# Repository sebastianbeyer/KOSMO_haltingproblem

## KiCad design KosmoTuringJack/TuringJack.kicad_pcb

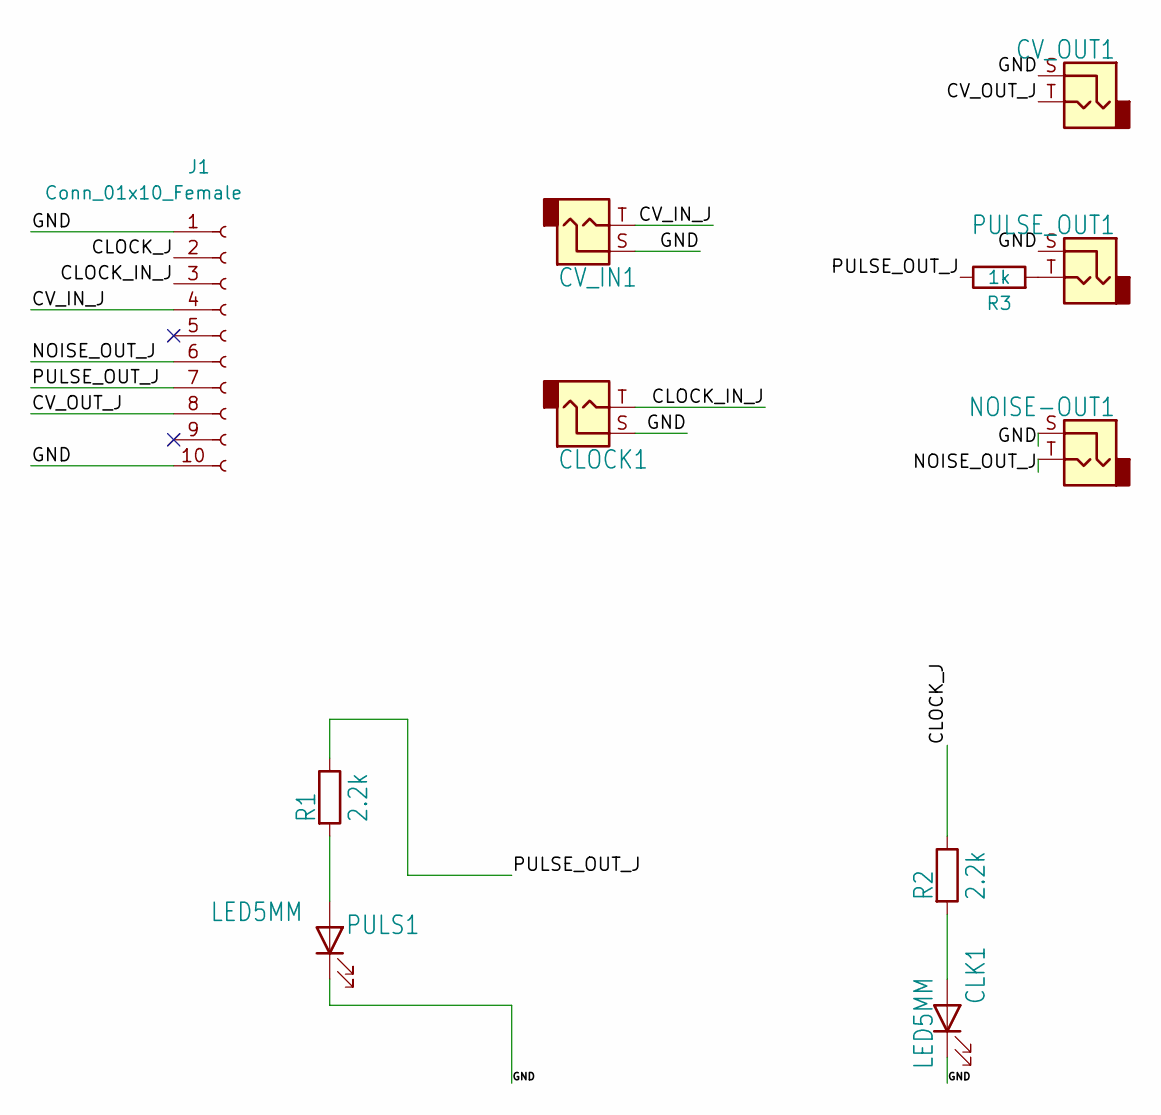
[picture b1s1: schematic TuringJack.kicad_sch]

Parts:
CLK1: LED5MM; LED_D5.0mm
CLOCK1: THONKICONNNEW; Jack_6.35mm_PJ_629HAN
CV_IN1: THONKICONNNEW; Jack_6.35mm_PJ_629HAN
CV_OUT1: THONKICONNNEW; Jack_6.35mm_PJ_629HAN
J1: Conn_01x10_Female; PinSocket_1x10_P2.54mm_Vertical
NOISE-OUT1: THONKICONNNEW; Jack_6.35mm_PJ_629HAN
PULS1: LED5MM; LED_D5.0mm
PULSE_OUT1: THONKICONNNEW; Jack_6.35mm_PJ_629HAN
R1, R2: 2.2k; R_Axial_DIN0207_L6.3mm_D2.5mm_P10.16mm_Horizontal
R3: 1k; R_Axial_DIN0207_L6.3mm_D2.5mm_P10.16mm_Horizontal

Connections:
/CLOCK_IN_J: CLOCK1.T, J1.3
/CLOCK_J: J1.2, R2.1
/CV_IN_J: CV_IN1.T, J1.4
/CV_OUT_J: CV_OUT1.T, J1.8
/GND: CLK1.1 (K), CLOCK1.S, CV_IN1.S, CV_OUT1.S, J1.1, J1.10, NOISE-OUT1.S, PULS1.1 (K), PULSE_OUT1.S
/NOISE_OUT_J: J1.6, NOISE-OUT1.T
/PULSE_OUT_J: J1.7, R1.1, R3.1
unnamed: CLK1.2 (A), R2.2
unnamed: PULS1.2 (A), R1.2
unnamed: PULSE_OUT1.T, R3.2

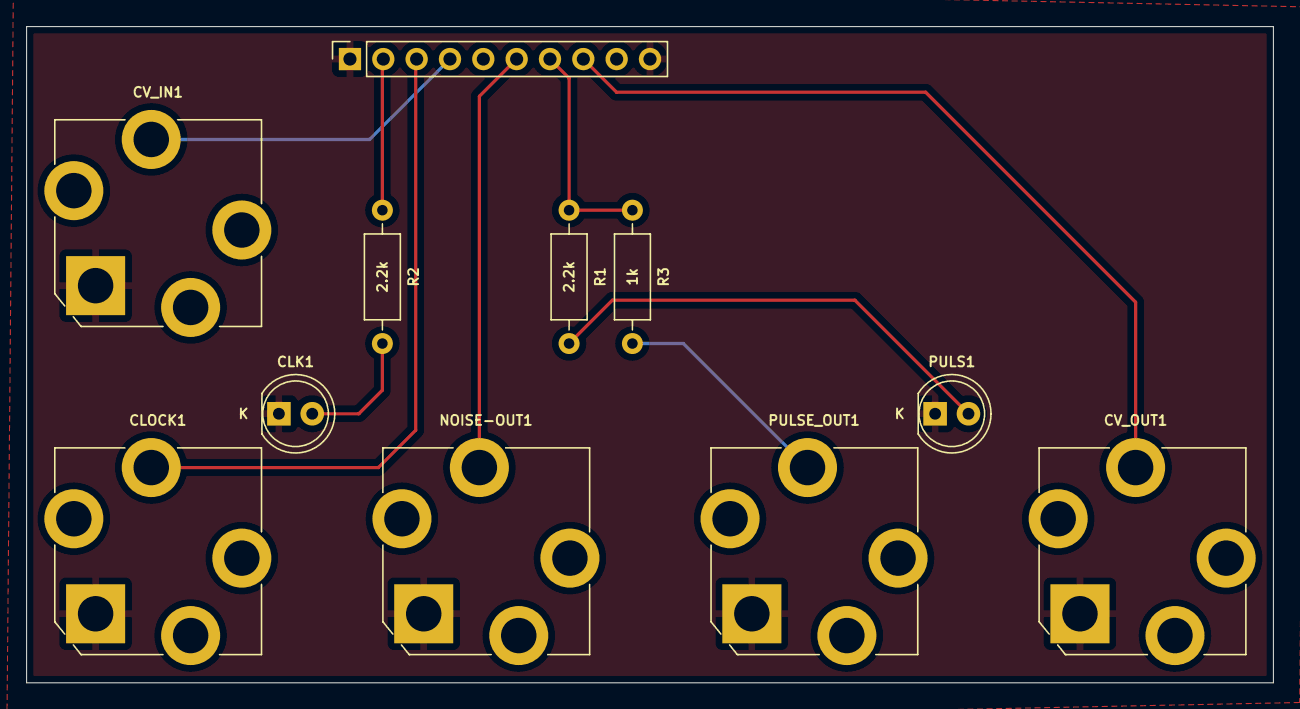
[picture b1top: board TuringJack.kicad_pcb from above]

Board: 2 copper layers, 95.0 x 50.0 mm, 11 parts (0 on the bottom side), 10 nets.

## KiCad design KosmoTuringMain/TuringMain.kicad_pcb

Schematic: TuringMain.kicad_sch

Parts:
AND_1, AND_2: 4081; DIL14
BUFFER1, BUFFER2: 4050; DIL16
C1, C5, C6, C7, C8, C13: 1n; C050-024X044
C2: 10n; C050-024X044
C3, C4, C15, C16, C17, C18, C19, C20, C21, C23, C24, C25, C26: 100n; C_Disc_D3.0mm_W1.6mm_P2.50mm
C9, C10, C12: 0.47uf; C050-035X075
C11: 330pf; C050-024X044
C14: 100n; C050-024X044
C22, C27: 10uf; CP_Radial_D6.3mm_P2.50mm
CHANGE1: 50k; Potentiometer_Alpha_RD901F-40-00D_Single_Vertical_centered
CLOCK1: THONKICONNNEW; Jack_6.35mm_PJ_629HAN
CV_IN1: THONKICONNNEW; Jack_6.35mm_PJ_629HAN
CV_OUT1: THONKICONNNEW; Jack_6.35mm_PJ_629HAN
D1: 1N4148; DO35-7
GATES1: MA08-2; IDC-Header_2x08_P2.54mm_Vertical
IC1: TL072P; DIL08
IC2, IC3: 78L09; TO-92_Inline_Wide
J1: Conn_01x10_Female; PinSocket_1x10_P2.54mm_Vertical
J2: Conn_01x10_Male; PinHeader_1x10_P2.54mm_Vertical
L1, L2: BL01RN1A
LENGTH1: ALPS-SRBV
NOISE-OUT1: THONKICONNNEW; Jack_6.35mm_PJ_629HAN
PULSES1: MA08-2; IDC-Header_2x08_P2.54mm_Vertical
PULSE_OUT1: THONKICONNNEW; Jack_6.35mm_PJ_629HAN
R1, R6, R7, R8, R12, R13, R14, R17, R23, R27: 10k; R_Axial_DIN0207_L6.3mm_D2.5mm_P10.16mm_Horizontal
R2: 3.3k; R_Axial_DIN0207_L6.3mm_D2.5mm_P10.16mm_Horizontal
R3, R5, R21, R24, R25: 100k; R_Axial_DIN0207_L6.3mm_D2.5mm_P10.16mm_Horizontal
R4, R9: 1.6k; R_Axial_DIN0207_L6.3mm_D2.5mm_P10.16mm_Horizontal
R10: 51k; R_Axial_DIN0207_L6.3mm_D2.5mm_P10.16mm_Horizontal
R11: 47k; R_Axial_DIN0207_L6.3mm_D2.5mm_P10.16mm_Horizontal
R15, R22, R26, R30: 1k; R_Axial_DIN0207_L6.3mm_D2.5mm_P10.16mm_Horizontal
R16: 5.1k; R_Axial_DIN0207_L6.3mm_D2.5mm_P10.16mm_Horizontal
R18: 68k; R_Axial_DIN0207_L6.3mm_D2.5mm_P10.16mm_Horizontal
R19, R29: 470k; R_Axial_DIN0207_L6.3mm_D2.5mm_P10.16mm_Horizontal
R20, R28: 15k; R_Axial_DIN0207_L6.3mm_D2.5mm_P10.16mm_Horizontal
R31, R32, R33, R34, R35, R36, R37, R38: 2.2k; R_Axial_DIN0207_L6.3mm_D2.5mm_P10.16mm_Horizontal
SCALE1: 50k; Potentiometer_Alpha_RD901F-40-00D_Single_Vertical_centered
SHIFTREG_EXT1: 4015; DIL16
SHIFTREG_MAIN1: 4015; DIL16
SV1: 10_PIN_HEADER; Power_Header
SWITCH_IC1: 4016; DIL14
T1: 2N3904; TO-92_Inline_Wide
TL1: TL431CLP; TO-92_Inline_Wide
U1: TL074_; DIL14
U$1: DAC0800; DIL16
UNK1, UNK2, UNK3, UNK4, UNK5, UNK6, UNK7, UNK8: LED5MM; LED_D5.0mm
VR1: 1M; Potentiometer_Bourns_3296W_Vertical_screw_centered
WRITE1: T-80-T-SPDT-ON-OFF-ON; SPDT-toggle-switch-1M-series

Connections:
/+12V: AND_1.14 (VDD), AND_2.14 (VDD), C3.2, C15.2, C16.1, C17.1, C18.1, C19.1, C20.1, C21.2, C22.1, GATES1.15, GATES1.16, IC1.8 (V+), IC2.3 (VI), IC3.3 (VI), L1.2, PULSES1.15, PULSES1.16, R1.2, R2.1, R7.2, R12.2, R18.1, R21.1, SHIFTREG_EXT1.16 (VDD), SHIFTREG_MAIN1.16 (VDD), SWITCH_IC1.14 (VDD), U1.4 (V+), U$1.13 (V+), WRITE1.1 (O)
/+12V_INLET: L1.1, SV1.9 (+12V), SV1.10 (+12V)
/-12V: C2.2, C4.2, C25.1, C26.2, C27.2, GATES1.11, GATES1.12, IC1.4 (V-), L2.2, PULSES1.11, PULSES1.12, R6.2, U1.11 (V-), U$1.3 (V-)
/-12V_INLET: L2.1, SV1.1 (-12V), SV1.2 (-12V)
/B1: AND_1.1 (I0), BUFFER1.9 (I), LENGTH1.F (6), R14.1, SHIFTREG_MAIN1.2 (QD), U$1.5 (B1-MSB), UNK8.2 (A)
/B2: AND_1.12 (I0), BUFFER1.11 (I), SHIFTREG_MAIN1.11 (QC), U$1.6 (B2), UNK4.2 (A)
/B3: AND_1.5 (I0), BUFFER1.7 (I), LENGTH1.E (5), SHIFTREG_MAIN1.12 (QB), U$1.7 (B3), UNK7.2 (A)
/B4: AND_1.8 (I0), BUFFER1.5 (I), LENGTH1.D (4), SHIFTREG_MAIN1.13 (QA), U$1.8 (B4), UNK3.2 (A)
/B5: AND_2.12 (I0), BUFFER2.11 (I), LENGTH1.C (3), R8.1, SHIFTREG_MAIN1.10 (QD), U$1.9 (B5), UNK6.2 (A)
/B6: AND_2.8 (I0), BUFFER2.9 (I), LENGTH1.B (2), SHIFTREG_MAIN1.3 (QC), U$1.10 (B6), UNK2.2 (A)
/B7: AND_2.5 (I0), BUFFER2.7 (I), LENGTH1.A (1), SHIFTREG_MAIN1.4 (QB), U$1.11 (B7), UNK5.2 (A)
/B8: AND_2.1 (I0), BUFFER2.5 (I), SHIFTREG_MAIN1.5 (QA), U$1.12 (B8-LSB), UNK1.2 (A)
/BUFFCLK: AND_1.2 (I1), AND_1.6 (I1), AND_1.9 (I1), AND_1.13 (I1), BUFFER2.2 (O), PULSES1.9, PULSES1.10
/BUFFCLK2: AND_2.2 (I1), AND_2.6 (I1), AND_2.9 (I1), AND_2.13 (I1), BUFFER1.2 (O), GATES1.9, GATES1.10
/CLOCK: BUFFER1.3 (I), BUFFER2.3 (I), D1.C, J2.2, R19.1, R27.1, SHIFTREG_EXT1.1 (CLK), SHIFTREG_EXT1.9 (CLK), SHIFTREG_MAIN1.1 (CLK), SHIFTREG_MAIN1.9 (CLK)
/CLOCK_IN: J2.3, R20.1
/CV_IN: J2.4, R10.1
/CV_OUT: CV_OUT1.T, J2.8, R15.1
/END_OF_LOOP: LENGTH1.COM (A), LENGTH1.COM2 (A), SWITCH_IC1.1 (A), SWITCH_IC1.5 (C)
/GATE1: BUFFER2.4 (O), GATES1.1
/GATE2: BUFFER2.6 (O), GATES1.2
/GATE3: BUFFER2.10 (O), GATES1.3
/GATE4: BUFFER2.12 (O), GATES1.4
/GATE5: BUFFER1.4 (O), GATES1.5
/GATE6: BUFFER1.6 (O), GATES1.6
/GATE7: BUFFER1.12 (O), GATES1.7
/GATE8: BUFFER1.10 (O), GATES1.8
/LOOP_CTRL: IC1.2 (-IN), R3.2, R10.2, R11.1
/NOISE: C9.2, IC1.5 (+IN), R24.2, R26.2
/NOISE_OUT: J2.6, R26.1
/PULSE1: AND_2.3 (O), BUFFER1.14 (I), PULSES1.1
/PULSE2: AND_2.4 (O), PULSES1.2
/PULSE3: AND_2.10 (O), PULSES1.3
/PULSE4: AND_2.11 (O), PULSES1.4
/PULSE5: AND_1.10 (O), PULSES1.5
/PULSE6: AND_1.4 (O), PULSES1.6
/PULSE7: AND_1.11 (O), PULSES1.7
/PULSE8: AND_1.3 (O), PULSES1.8
/PULSE_OUT: BUFFER1.15 (O), J2.7
/START_OF_LOOP: C5.2, R13.1, R30.2, SHIFTREG_MAIN1.7 (D)
/STEP_12: C8.2, LENGTH1.G (7), R17.2, SHIFTREG_EXT1.15 (D)
/STEP_16: LENGTH1.H (8), SHIFTREG_EXT1.2 (QD)
GND: AND_1.7 (VSS), AND_2.7 (VSS), BUFFER1.8 (VSS), BUFFER2.8 (VSS), BUFFER2.14 (I), C1.1, C3.1, C4.1, C5.1, C6.1, C8.1, C11.1, C14.1, C15.1, C16.2, C17.2, C18.2, C19.2, C20.2, C21.1, C22.2, C23.1, C24.1, C25.2, C26.1, C27.1, CLOCK1.S, CV_IN1.S, CV_OUT1.S, GATES1.13, GATES1.14, IC1.3 (+IN), IC2.2 (GND), IC3.2 (GND), J1.1, J1.10, J2.1, J2.10, NOISE-OUT1.S, PULSES1.13, PULSES1.14, PULSE_OUT1.S, R9.1, R24.1, R25.1, R27.2, R28.1, R31.2, R32.2, R33.2, R34.2, R35.1, R36.1, R37.1, R38.1, SCALE1.1, SHIFTREG_EXT1.6 (RES), SHIFTREG_EXT1.8 (VSS), SHIFTREG_EXT1.14 (RES), SHIFTREG_MAIN1.6 (RES), SHIFTREG_MAIN1.8 (VSS), SHIFTREG_MAIN1.14 (RES), SV1.3 (GND), SV1.4 (GND), SV1.5 (GND), SV1.6 (GND), SV1.7 (GND), SV1.8 (GND), SWITCH_IC1.3 (B), SWITCH_IC1.7 (VSS), SWITCH_IC1.9 (B), T1.2 (B), TL1.2 (A), U1.3 (+IN), U1.10 (+IN), U1.12 (+IN), U$1.1 (VLC), U$1.2 (IOUT), WRITE1.3 (S)
unnamed: BUFFER1.1 (VDD), C23.2, IC2.1 (VO)
unnamed: BUFFER2.1 (VDD), C24.2, IC3.1 (VO)
unnamed: C1.2, R8.2, SHIFTREG_MAIN1.15 (D)
unnamed: C2.1, U$1.16 (COMP)
unnamed: C6.2, R14.2, SHIFTREG_EXT1.7 (D)
unnamed: C7.1, R16.1, U1.2 (-IN), U$1.4 (IOUTB)
unnamed: C7.2, R16.2, SCALE1.3, U1.1 (OUT)
unnamed: C10.1, R29.1, U1.8 (OUT)
unnamed: C10.2, R22.2
unnamed: C11.2, R19.2, R20.2, R25.2, U1.5 (+IN)
unnamed: C12.1, R23.1
unnamed: C12.2, R21.2, T1.1 (E)
unnamed: C13.1, R22.1, U1.13 (-IN), VR1.1
unnamed: C9.1, C13.2, U1.14 (OUT), VR1.2, VR1.3
unnamed: C14.2, R18.2, R28.2, U1.6 (-IN)
unnamed: CHANGE1.1, R6.1
unnamed: CHANGE1.2, R3.1
unnamed: CHANGE1.3, R1.1
unnamed: CLOCK1.T, J1.3
unnamed: CV_IN1.T, J1.4
unnamed: D1.A, U1.7 (OUT)
unnamed: IC1.1 (OUT), IC1.6 (-IN), R11.2
unnamed: IC1.7 (OUT), R5.2
unnamed: J1.6, NOISE-OUT1.T
unnamed: J1.7, PULSE_OUT1.T
unnamed: R2.2, R4.2, TL1.1 (REF), TL1.3 (K)
unnamed: R4.1, U$1.14 (VREF+)
unnamed: R5.1, SWITCH_IC1.6 (C), SWITCH_IC1.13 (C)
unnamed: R7.1, SWITCH_IC1.4 (A), SWITCH_IC1.11 (A)
unnamed: R9.2, U$1.15 (VREF-)
unnamed: R12.1, SWITCH_IC1.8 (A), SWITCH_IC1.12 (C)
unnamed: R13.2, SWITCH_IC1.2 (B), SWITCH_IC1.10 (B)
unnamed: R15.2, SCALE1.2
unnamed: R17.1, SHIFTREG_EXT1.10 (QD)
unnamed: R23.2, R29.2, U1.9 (-IN)
unnamed: R30.1, WRITE1.2
unnamed: R31.1, UNK1.1 (K)
unnamed: R32.1, UNK5.1 (K)
unnamed: R33.1, UNK2.1 (K)
unnamed: R34.1, UNK6.1 (K)
unnamed: R35.2, UNK3.1 (K)
unnamed: R36.2, UNK7.1 (K)
unnamed: R37.2, UNK4.1 (K)
unnamed: R38.2, UNK8.1 (K)

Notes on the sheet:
Shift register loop
Length steps: 16 = step_16 12 = step_12 8 = B1 6 = B3 5 = B4 4 = B5 3 = B6 2 = B7
Randomised invert/loop switching
/Users/aash/Dropbox/Electronics/~{MODULAR/design/logo} copy.bmp
DAC
NB: Bit numbers are reversed at this point: Bit8 = first bit (left hand LED on main module) becomes Pulse1 (Top output on expanders)
Clock input
Noise Generator

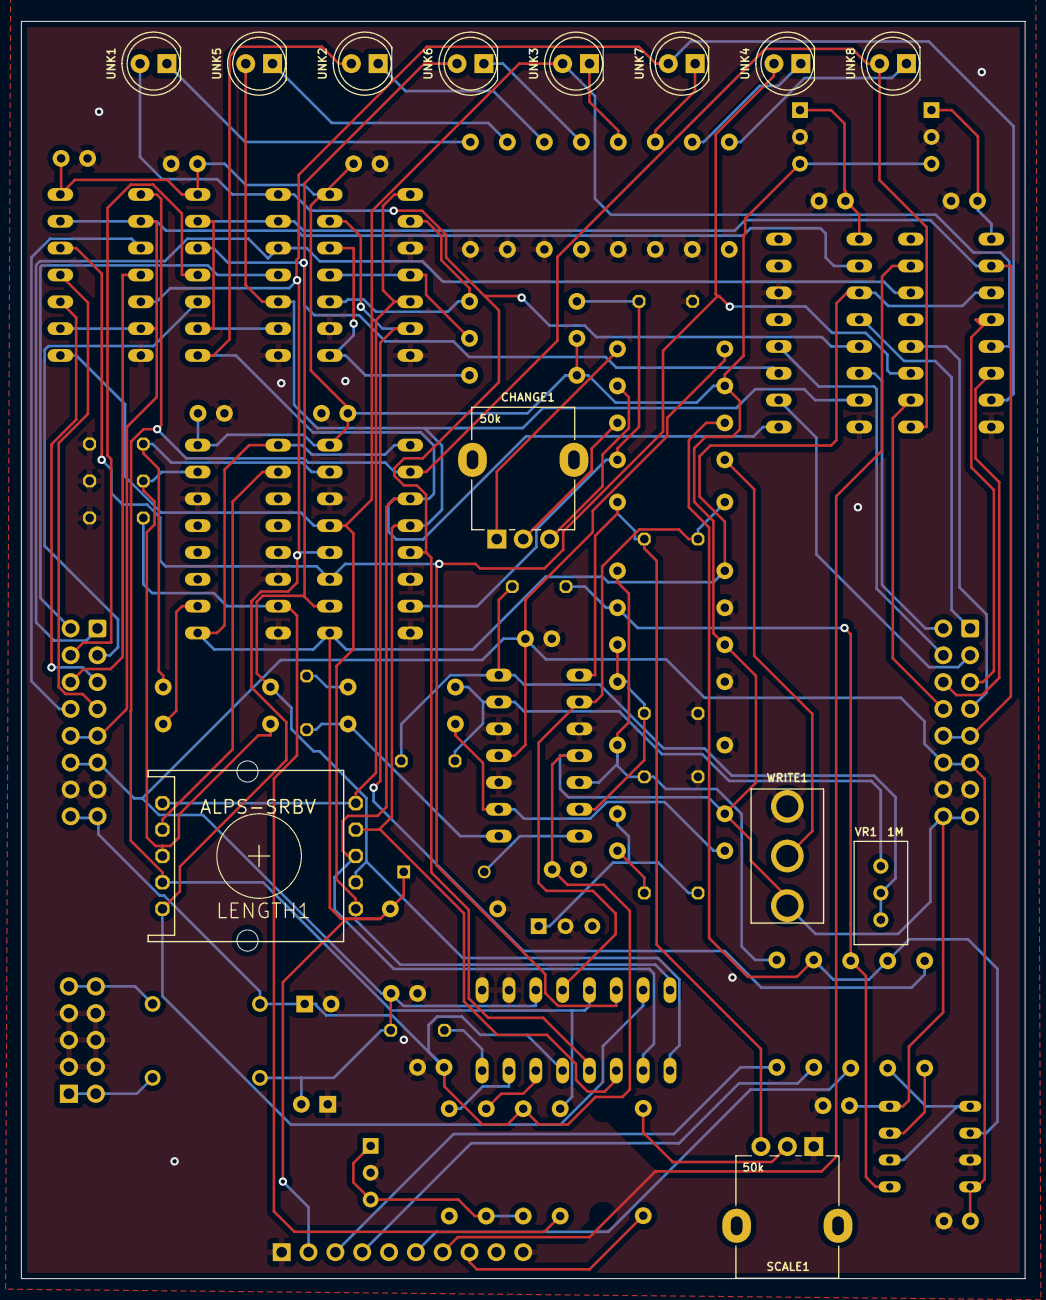
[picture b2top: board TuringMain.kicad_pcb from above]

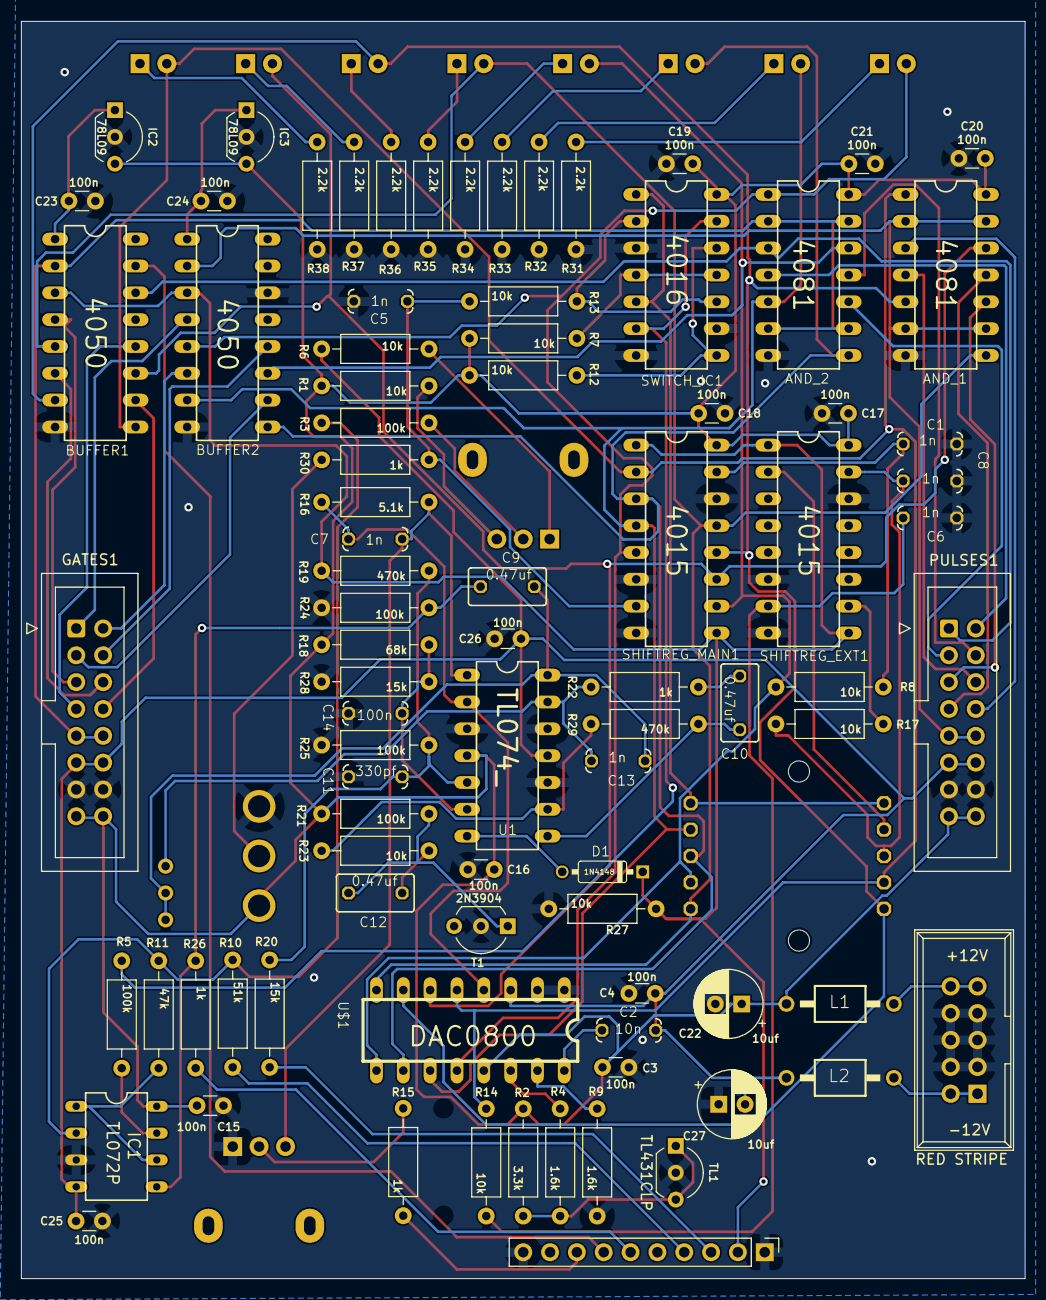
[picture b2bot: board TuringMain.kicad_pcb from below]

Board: 2 copper layers, 95.0 x 119.0 mm, 99 parts (86 on the bottom side), 83 nets.

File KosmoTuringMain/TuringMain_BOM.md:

# TuringMain.kicad_sch BOM

Tue 13 Dec 2022 11:17:51 CET

Generated from schematic by Eeschema 6.0.8-f2edbf62ab~116~ubuntu22.04.1

**Component Count:** 105

| Refs | Qty | Component | Description | Vendor | SKU |
| ----- | --- | ---- | ----------- | ---- | ---- |
| AND_1, AND_2 | 2 | 4081 |  |  |  |
| BUFFER1, BUFFER2 | 2 | 4050 |  |  |  |
| C1, C5, C6, C7, C8, C13 | 6 | 1n |  |  |  |
| C2 | 1 | 10n |  |  |  |
| C3, C4, C15, C16, C17, C18, C19, C20, C21, C23, C24, C25, C26 | 13 | 100n |  |  |  |
| C9, C10, C12 | 3 | 0.47uf |  |  |  |
| C11 | 1 | 330pf |  |  |  |
| C14 | 1 | 100n |  |  |  |
| C22, C27 | 2 | 10uf | Polarized capacitor | Tayda |  |
| CHANGE1, SCALE1 | 2 | 50k | Potentiometer | Tayda |  |
| CLOCK1, CV_IN1, CV_OUT1, NOISE-OUT1, PULSE_OUT1 | 5 | THONKICONNNEW | Audio Jack, 2 Poles (Mono / TS) | Tayda | A-1121 |
| D1 | 1 | 1N4148 |  |  |  |
| GATES1 | 1 | MA08-2 | Generic connector, double row, 02x08, odd/even pin numbering scheme (row 1 odd numbers, row 2 even numbers), script generated (kicad-library-utils/schlib/autogen/connector/) |  |  |
| IC1 | 1 | TL072P |  |  |  |
| IC2, IC3 | 2 | 78L09 | Positive 100mA 30V Linear Regulator, Fixed Output 5V, TO-92 | Tayda | A-176 |
| J1 | 1 | Conn_01x10_Female | Generic connector, single row, 01x10, script generated (kicad-library-utils/schlib/autogen/connector/) |  |  |
| J2 | 1 | Conn_01x10_Male | Generic connector, single row, 01x10, script generated (kicad-library-utils/schlib/autogen/connector/) |  |  |
| L1, L2 | 2 | BL01RN1A |  |  |  |
| LENGTH1 | 1 | ALPS-SRBV |  |  |  |
| PULSES1 | 1 | MA08-2 |  |  |  |
| R1, R6, R7, R8, R12, R13, R14, R17, R23, R27 | 10 | 10k | Resistor | Tayda |  |
| R2 | 1 | 3.3k | Resistor | Tayda |  |
| R3, R5, R21, R25 | 4 | 100k | Resistor | Tayda |  |
| R4, R9 | 2 | 1.6k | Resistor | Tayda |  |
| R10 | 1 | 51k | Resistor | Tayda |  |
| R11 | 1 | 47k | Resistor | Tayda |  |
| R15, R22, R26, R30 | 4 | 1k | Resistor | Tayda |  |
| R16 | 1 | 5.1k | Resistor | Tayda |  |
| R18 | 1 | 68k | Resistor | Tayda |  |
| R19, R29 | 2 | 470k | Resistor | Tayda |  |
| R20, R28 | 2 | 15k | Resistor | Tayda |  |
| R24 | 1 | 100k |  |  |  |
| R31, R32, R33, R34, R35, R36, R37, R38 | 8 | 2.2k | Resistor | Tayda |  |
| SHIFTREG_EXT1, SHIFTREG_MAIN1 | 2 | 4015 |  |  |  |
| SV1 | 1 | 10_PIN_HEADER | Pin header 2.54 mm 2x5 | Tayda | A-2939 |
| SWITCH_IC1 | 1 | 4016 |  |  |  |
| T1 | 1 | 2N3904 | Small Signal NPN Transistor, TO-92 | Tayda | A-111 |
| TL1 | 1 | TL431CLP | Shunt Regulator, TO-92 |  |  |
| U1 | 1 | TL074_ |  |  |  |
| U$1 | 1 | DAC0800 |  |  |  |
| UNK1, UNK2, UNK3, UNK4, UNK5, UNK6, UNK7, UNK8 | 8 | LED5MM | Light emitting diode | Tayda | A-1553 |
| VR1 | 1 | 1M |  |  |  |
| WRITE1 | 1 | T-80-T-SPDT-ON-OFF-ON |  |  |  |

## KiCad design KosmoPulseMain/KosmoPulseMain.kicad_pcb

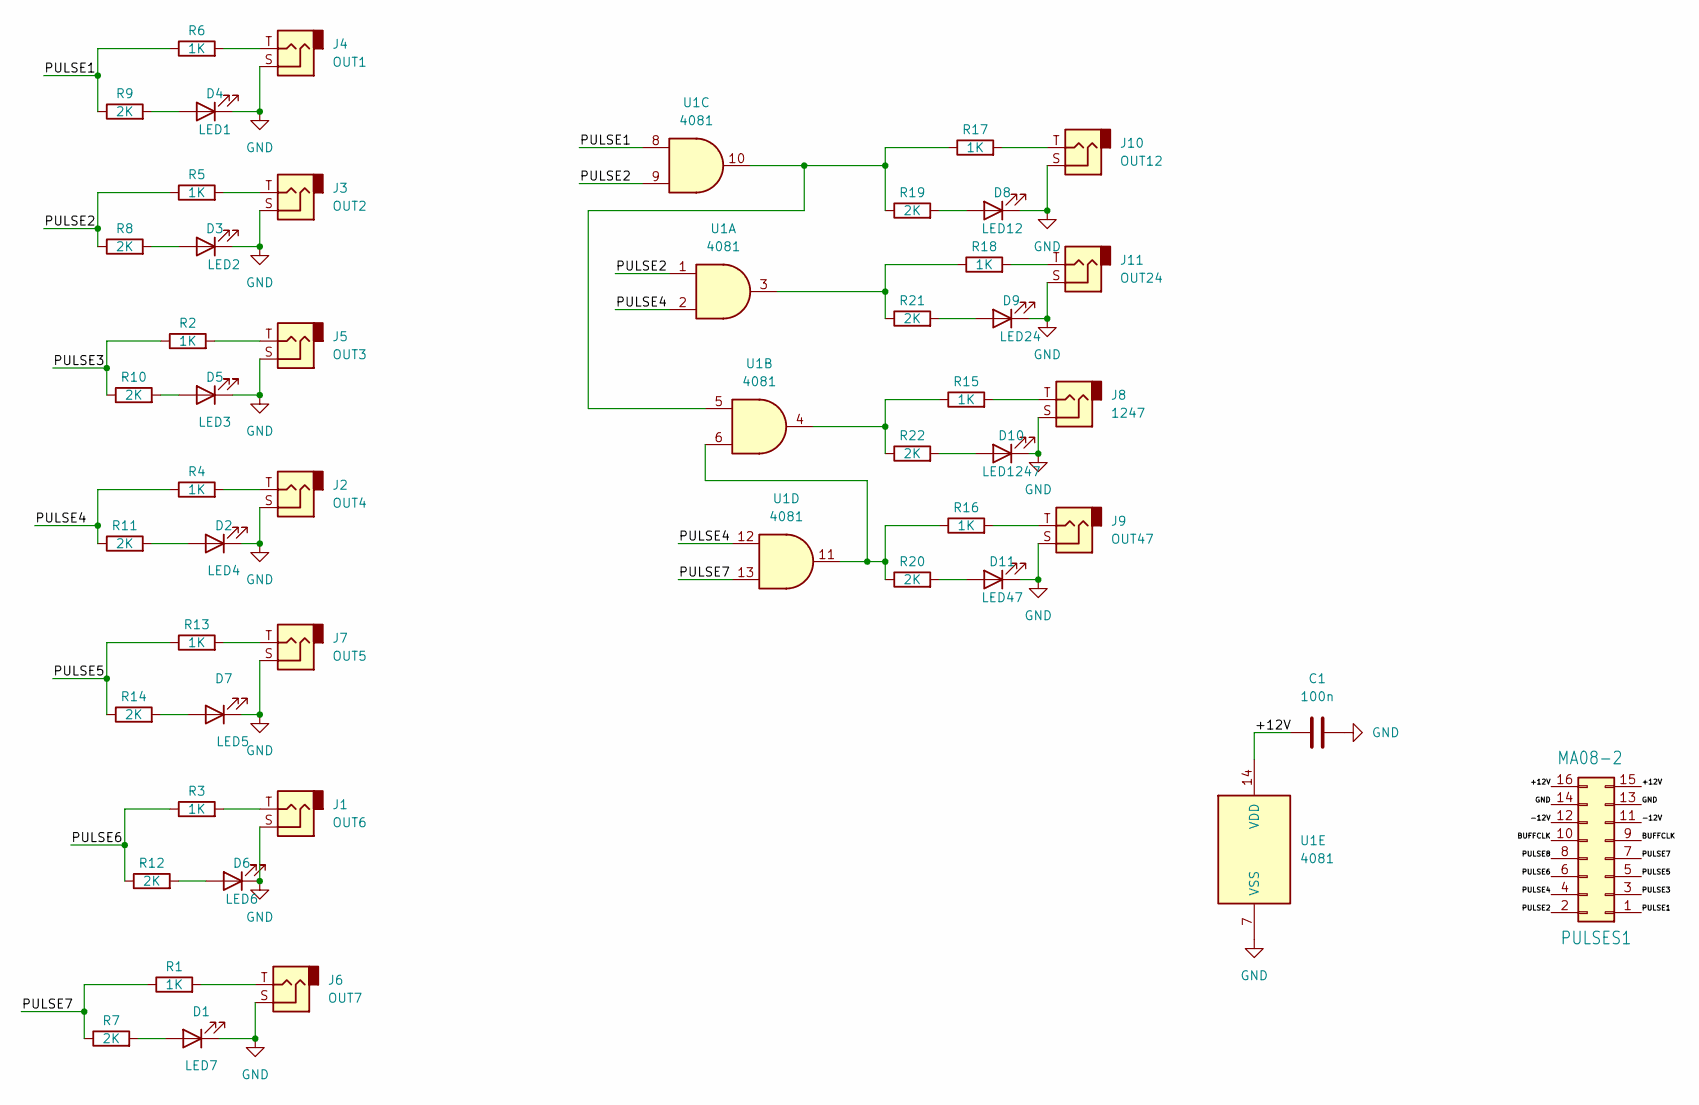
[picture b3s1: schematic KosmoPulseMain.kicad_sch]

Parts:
C1: 100n; C_Disc_D3.0mm_W1.6mm_P2.50mm
D1: LED7; LED_D5.0mm
D2: LED4; LED_D5.0mm
D3: LED2; LED_D5.0mm
D4: LED1; LED_D5.0mm
D5: LED3; LED_D5.0mm
D6: LED6; LED_D5.0mm
D7: LED5; LED_D5.0mm
D8: LED12; LED_D5.0mm
D9: LED24; LED_D5.0mm
D10: LED1247; LED_D5.0mm
D11: LED47; LED_D5.0mm
J1: OUT6; Jack_6.35mm_PJ_629HAN
J2: OUT4; Jack_6.35mm_PJ_629HAN
J3: OUT2; Jack_6.35mm_PJ_629HAN
J4: OUT1; Jack_6.35mm_PJ_629HAN
J5: OUT3; Jack_6.35mm_PJ_629HAN
J6: OUT7; Jack_6.35mm_PJ_629HAN
J7: OUT5; Jack_6.35mm_PJ_629HAN
J8: 1247; Jack_6.35mm_PJ_629HAN
J9: OUT47; Jack_6.35mm_PJ_629HAN
J10: OUT12; Jack_6.35mm_PJ_629HAN
J11: OUT24; Jack_6.35mm_PJ_629HAN
PULSES1: MA08-2; IDC-Header_2x08_P2.54mm_Vertical
R1, R2, R3, R4, R5, R6, R13, R15, R16, R17, R18: 1K; R_Axial_DIN0207_L6.3mm_D2.5mm_P2.54mm_Vertical
R7, R8, R9, R10, R11, R12, R14, R19, R20, R21, R22: 2K; R_Axial_DIN0207_L6.3mm_D2.5mm_P10.16mm_Horizontal
U1: 4081; DIP-14_W7.62mm_Socket_LongPads

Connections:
/+12V: C1.1, PULSES1.15, PULSES1.16, U1.14 (VDD)
/-12V: PULSES1.11, PULSES1.12
/BUFFCLK: PULSES1.9, PULSES1.10
/PULSE1: PULSES1.1, R6.1, R9.1, U1.8
/PULSE2: PULSES1.2, R5.1, R8.1, U1.1, U1.9
/PULSE3: PULSES1.3, R2.1, R10.1
/PULSE4: PULSES1.4, R4.1, R11.1, U1.2, U1.12
/PULSE5: PULSES1.5, R13.1, R14.1
/PULSE6: PULSES1.6, R3.1, R12.1
/PULSE7: PULSES1.7, R1.1, R7.1, U1.13
/PULSE8: PULSES1.8
GND: C1.2, D1.1 (K), D2.1 (K), D3.1 (K), D4.1 (K), D5.1 (K), D6.1 (K), D7.1 (K), D8.1 (K), D9.1 (K), D10.1 (K), D11.1 (K), J1.S, J2.S, J3.S, J4.S, J5.S, J6.S, J7.S, J8.S, J9.S, J10.S, J11.S, PULSES1.13, PULSES1.14, U1.7 (VSS)
unnamed: D1.2 (A), R7.2
unnamed: D2.2 (A), R11.2
unnamed: D3.2 (A), R8.2
unnamed: D4.2 (A), R9.2
unnamed: D5.2 (A), R10.2
unnamed: D6.2 (A), R12.2
unnamed: D7.2 (A), R14.2
unnamed: D8.2 (A), R19.2
unnamed: D9.2 (A), R21.2
unnamed: D10.2 (A), R22.2
unnamed: D11.2 (A), R20.2
unnamed: J1.T, R3.2
unnamed: J2.T, R4.2
unnamed: J3.T, R5.2
unnamed: J4.T, R6.2
unnamed: J5.T, R2.2
unnamed: J6.T, R1.2
unnamed: J7.T, R13.2
unnamed: J8.T, R15.2
unnamed: J9.T, R16.2
unnamed: J10.T, R17.2
unnamed: J11.T, R18.2
unnamed: R15.1, R22.1, U1.4
unnamed: R16.1, R20.1, U1.6, U1.11
unnamed: R17.1, R19.1, U1.5, U1.10
unnamed: R18.1, R21.1, U1.3

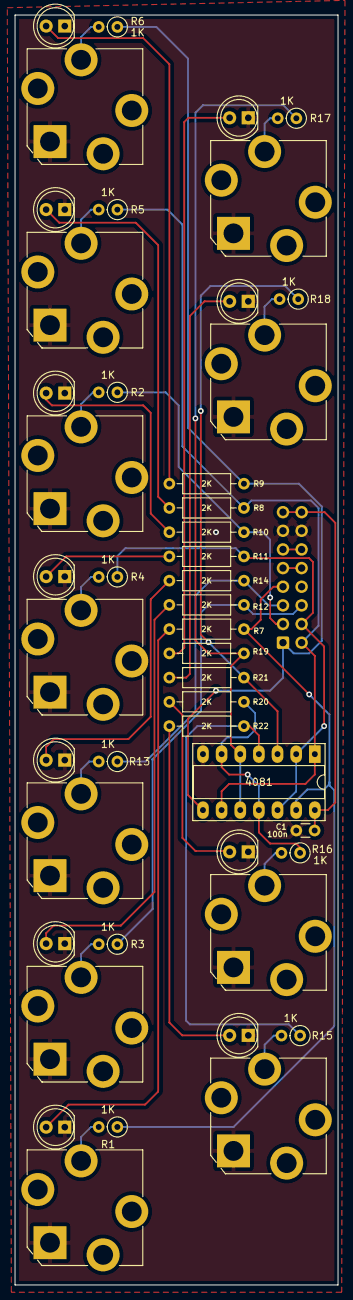
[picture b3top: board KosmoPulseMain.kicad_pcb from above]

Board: 2 copper layers, 44.0 x 173.0 mm, 47 parts (1 on the bottom side), 37 nets.

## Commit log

2022-09-13 initial
2022-09-13 add turing main panel
2022-09-13 add jack board
2022-09-13 add pulse addon board
2022-09-23 fix #1 missing cathode connection of clock led
2022-09-26 move pulse out 1k resistor after the led, so it does not act as voltage divider, thanks @holmesrichards !
2022-12-13 add BOM

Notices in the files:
KosmoTuringJack/TuringJack.kicad_pcb:
February 2016 CC-BY-SA
